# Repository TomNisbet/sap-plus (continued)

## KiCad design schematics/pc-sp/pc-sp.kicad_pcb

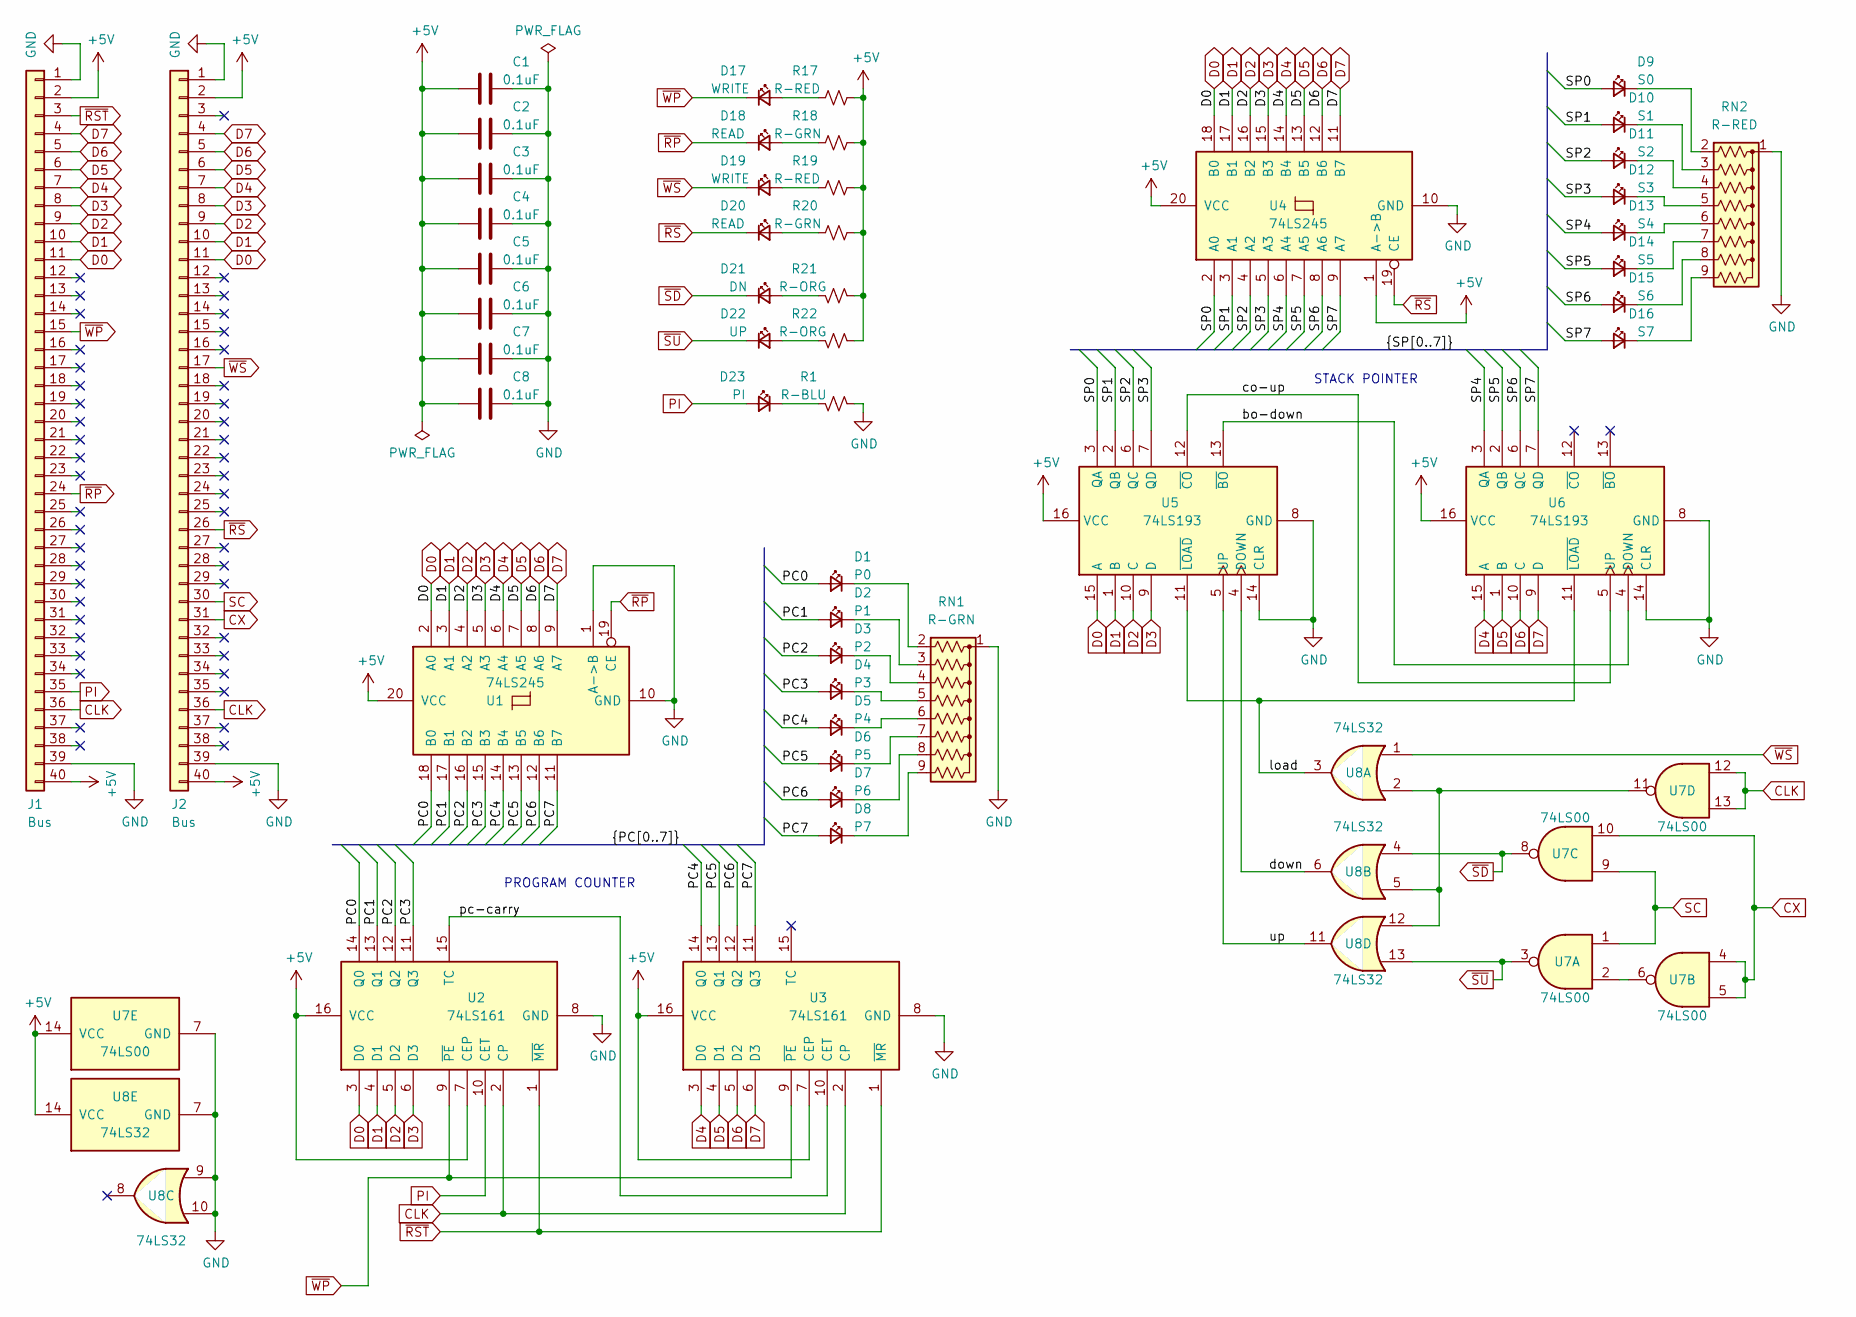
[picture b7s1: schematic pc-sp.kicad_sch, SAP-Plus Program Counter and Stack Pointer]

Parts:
C1, C2, C3, C4, C5, C6, C7, C8: 0.1uF; C_Disc_D3.0mm_W1.6mm_P2.50mm
D1: P0; LED_D3.0mm
D2: P1; LED_D3.0mm
D3: P2; LED_D3.0mm
D4: P3; LED_D3.0mm
D5: P4; LED_D3.0mm
D6: P5; LED_D3.0mm
D7: P6; LED_D3.0mm
D8: P7; LED_D3.0mm
D9: S0; LED_D3.0mm
D10: S1; LED_D3.0mm
D11: S2; LED_D3.0mm
D12: S3; LED_D3.0mm
D13: S4; LED_D3.0mm
D14: S5; LED_D3.0mm
D15: S6; LED_D3.0mm
D16: S7; LED_D3.0mm
D17, D19: WRITE; LED_D3.0mm
D18, D20: READ; LED_D3.0mm
D21: DN; LED_D3.0mm
D22: UP; LED_D3.0mm
D23: PI; LED_D3.0mm
J1, J2: Bus; PinHeader_1x40_P2.54mm_Vertical
R1: R-BLU; R_Axial_DIN0207_L6.3mm_D2.5mm_P10.16mm_Horizontal
R17, R19: R-RED; R_Axial_DIN0207_L6.3mm_D2.5mm_P10.16mm_Horizontal
R18, R20: R-GRN; R_Axial_DIN0207_L6.3mm_D2.5mm_P10.16mm_Horizontal
R21, R22: R-ORG; R_Axial_DIN0207_L6.3mm_D2.5mm_P10.16mm_Horizontal
RN1: R-GRN; R_Array_SIP9
RN2: R-RED; R_Array_SIP9
U1, U4: 74LS245; DIP-20_W7.62mm
U2, U3: 74LS161; DIP-16_W7.62mm
U5, U6: 74LS193; DIP-16_W7.62mm
U7: 74LS00; DIP-14_W7.62mm
U8: 74LS32; DIP-14_W7.62mm

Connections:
+5V: C1.2, C2.2, C3.2, C4.2, C5.2, C6.2, C7.2, C8.2, J1.2, J1.40, J2.2, J2.40, R17.1, R18.1, R19.1, R20.1, R21.2, R22.2, U1.20 (VCC), U2.7 (CEP), U2.16 (VCC), U3.7 (CEP), U3.16 (VCC), U4.1 (A->B), U4.20 (VCC), U5.16 (VCC), U6.16 (VCC), U7.14 (VCC), U8.14 (VCC)
/PC0: D1.2 (A), U1.18 (B0), U2.14 (Q0)
/PC1: D2.2 (A), U1.17 (B1), U2.13 (Q1)
/PC2: D3.2 (A), U1.16 (B2), U2.12 (Q2)
/PC3: D4.2 (A), U1.15 (B3), U2.11 (Q3)
/PC4: D5.2 (A), U1.14 (B4), U3.14 (Q0)
/PC5: D6.2 (A), U1.13 (B5), U3.13 (Q1)
/PC6: D7.2 (A), U1.12 (B6), U3.12 (Q2)
/PC7: D8.2 (A), U1.11 (B7), U3.11 (Q3)
/SP0: D9.2 (A), U4.2 (A0), U5.3 (QA)
/SP1: D10.2 (A), U4.3 (A1), U5.2 (QB)
/SP2: D11.2 (A), U4.4 (A2), U5.6 (QC)
/SP3: D12.2 (A), U4.5 (A3), U5.7 (QD)
/SP4: D13.2 (A), U4.6 (A4), U6.3 (QA)
/SP5: D14.2 (A), U4.7 (A5), U6.2 (QB)
/SP6: D15.2 (A), U4.8 (A6), U6.6 (QC)
/SP7: D16.2 (A), U4.9 (A7), U6.7 (QD)
/bo-down: U5.13 (~BO), U6.4 (DOWN)
/co-up: U5.12 (~CO), U6.5 (UP)
/down: U5.4 (DOWN), U8.6
/load: U5.11 (~LOAD), U6.11 (~LOAD), U8.3
/pc-carry: U2.15 (TC), U3.10 (CET)
/up: U5.5 (UP), U8.11
CLK: J1.36, J2.36, U2.2 (CP), U3.2 (CP), U7.12, U7.13
CX: J2.31, U7.4, U7.5, U7.10
D0: J1.11, J2.11, U1.2 (A0), U2.3 (D0), U4.18 (B0), U5.15 (A)
D1: J1.10, J2.10, U1.3 (A1), U2.4 (D1), U4.17 (B1), U5.1 (B)
D2: J1.9, J2.9, U1.4 (A2), U2.5 (D2), U4.16 (B2), U5.10 (C)
D3: J1.8, J2.8, U1.5 (A3), U2.6 (D3), U4.15 (B3), U5.9 (D)
D4: J1.7, J2.7, U1.6 (A4), U3.3 (D0), U4.14 (B4), U6.15 (A)
D5: J1.6, J2.6, U1.7 (A5), U3.4 (D1), U4.13 (B5), U6.1 (B)
D6: J1.5, J2.5, U1.8 (A6), U3.5 (D2), U4.12 (B6), U6.10 (C)
D7: J1.4, J2.4, U1.9 (A7), U3.6 (D3), U4.11 (B7), U6.9 (D)
GND: C1.1, C2.1, C3.1, C4.1, C5.1, C6.1, C7.1, C8.1, J1.1, J1.39, J2.1, J2.39, R1.2, RN1.1 (common), RN2.1 (common), U1.1 (A->B), U1.10 (GND), U2.8 (GND), U3.8 (GND), U4.10 (GND), U5.8 (GND), U5.14 (CLR), U6.8 (GND), U6.14 (CLR), U7.7 (GND), U8.7 (GND), U8.9, U8.10
unnamed: D1.1 (K), RN1.2 (R1)
unnamed: D2.1 (K), RN1.3 (R2)
unnamed: D3.1 (K), RN1.4 (R3)
unnamed: D4.1 (K), RN1.5 (R4)
unnamed: D5.1 (K), RN1.6 (R5)
unnamed: D6.1 (K), RN1.7 (R6)
unnamed: D7.1 (K), RN1.8 (R7)
unnamed: D8.1 (K), RN1.9 (R8)
unnamed: D9.1 (K), RN2.2 (R1)
unnamed: D10.1 (K), RN2.3 (R2)
unnamed: D11.1 (K), RN2.4 (R3)
unnamed: D12.1 (K), RN2.5 (R4)
unnamed: D13.1 (K), RN2.6 (R5)
unnamed: D14.1 (K), RN2.7 (R6)
unnamed: D15.1 (K), RN2.8 (R7)
unnamed: D16.1 (K), RN2.9 (R8)
unnamed: D17.2 (A), R17.2
unnamed: D18.2 (A), R18.2
unnamed: D19.2 (A), R19.2
unnamed: D20.2 (A), R20.2
unnamed: D21.2 (A), R21.1
unnamed: D22.2 (A), R22.1
unnamed: D23.1 (K), R1.1
unnamed: U7.2, U7.6
unnamed: U7.11, U8.2, U8.5, U8.12
PI: D23.2 (A), J1.35, U2.10 (CET)
SC: J2.30, U7.1, U7.9
~RP: D18.1 (K), J1.24, U1.19 (CE)
~RST: J1.3, U2.1 (~MR), U3.1 (~MR)
~RS: D20.1 (K), J2.26, U4.19 (CE)
~SD: D21.1 (K), U7.8, U8.4
~SU: D22.1 (K), U7.3, U8.13
~WP: D17.1 (K), J1.15, U2.9 (~PE), U3.9 (~PE)
~WS: D19.1 (K), J2.17, U8.1

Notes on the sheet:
PROGRAM COUNTER
STACK POINTER

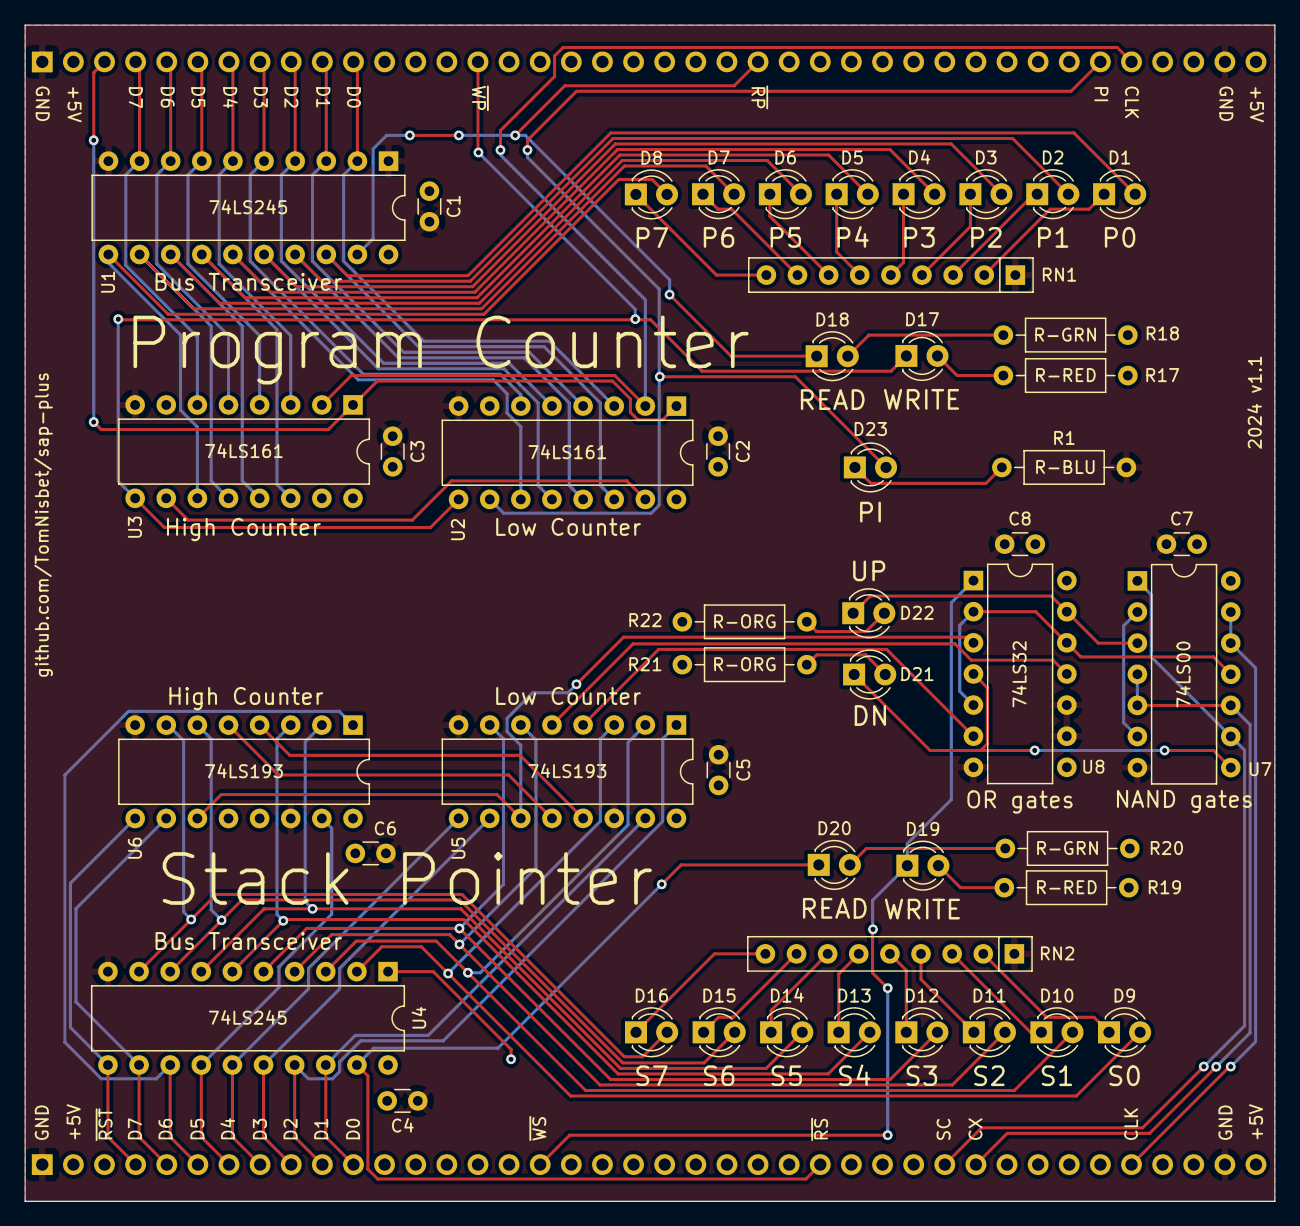
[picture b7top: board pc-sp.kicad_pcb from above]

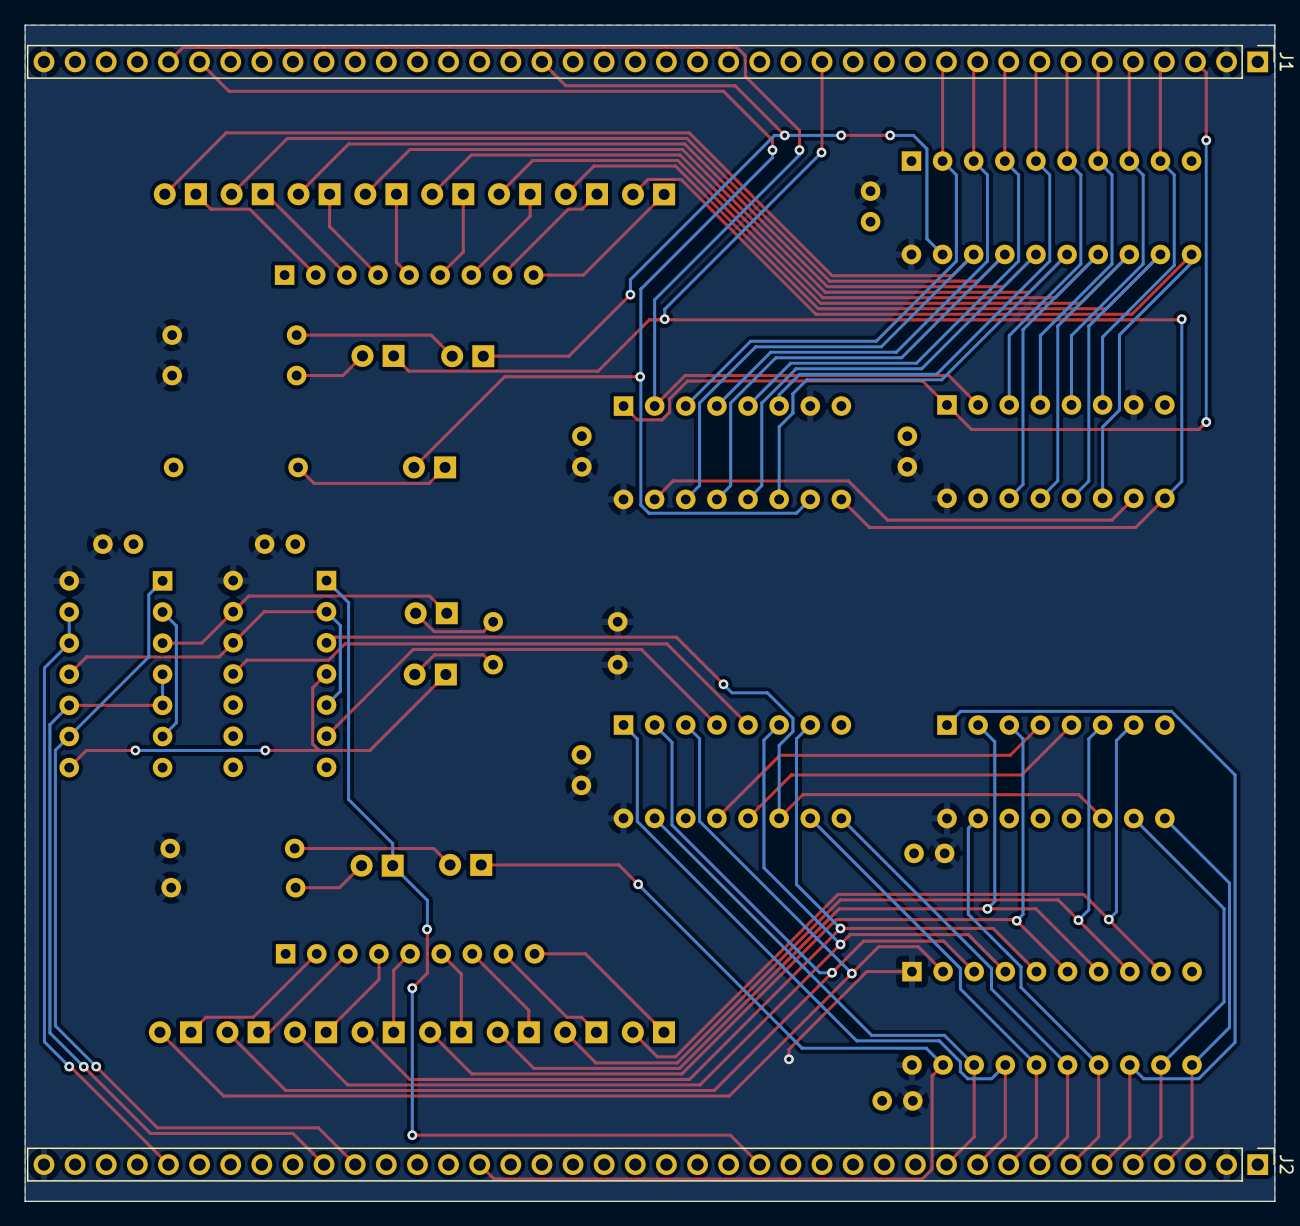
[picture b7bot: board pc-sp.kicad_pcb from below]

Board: 2 copper layers, 102.0 x 96.0 mm, 50 parts (2 on the bottom side), 68 nets.

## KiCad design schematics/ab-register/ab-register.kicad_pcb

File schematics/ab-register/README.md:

# A and B Register Module schematics

created with KiCad 8.0

## Changelog

### 1.1

* Fix polarity of BI LED
* Add module interconnect labels
* Add BI text box

### 1.0

* Initial version

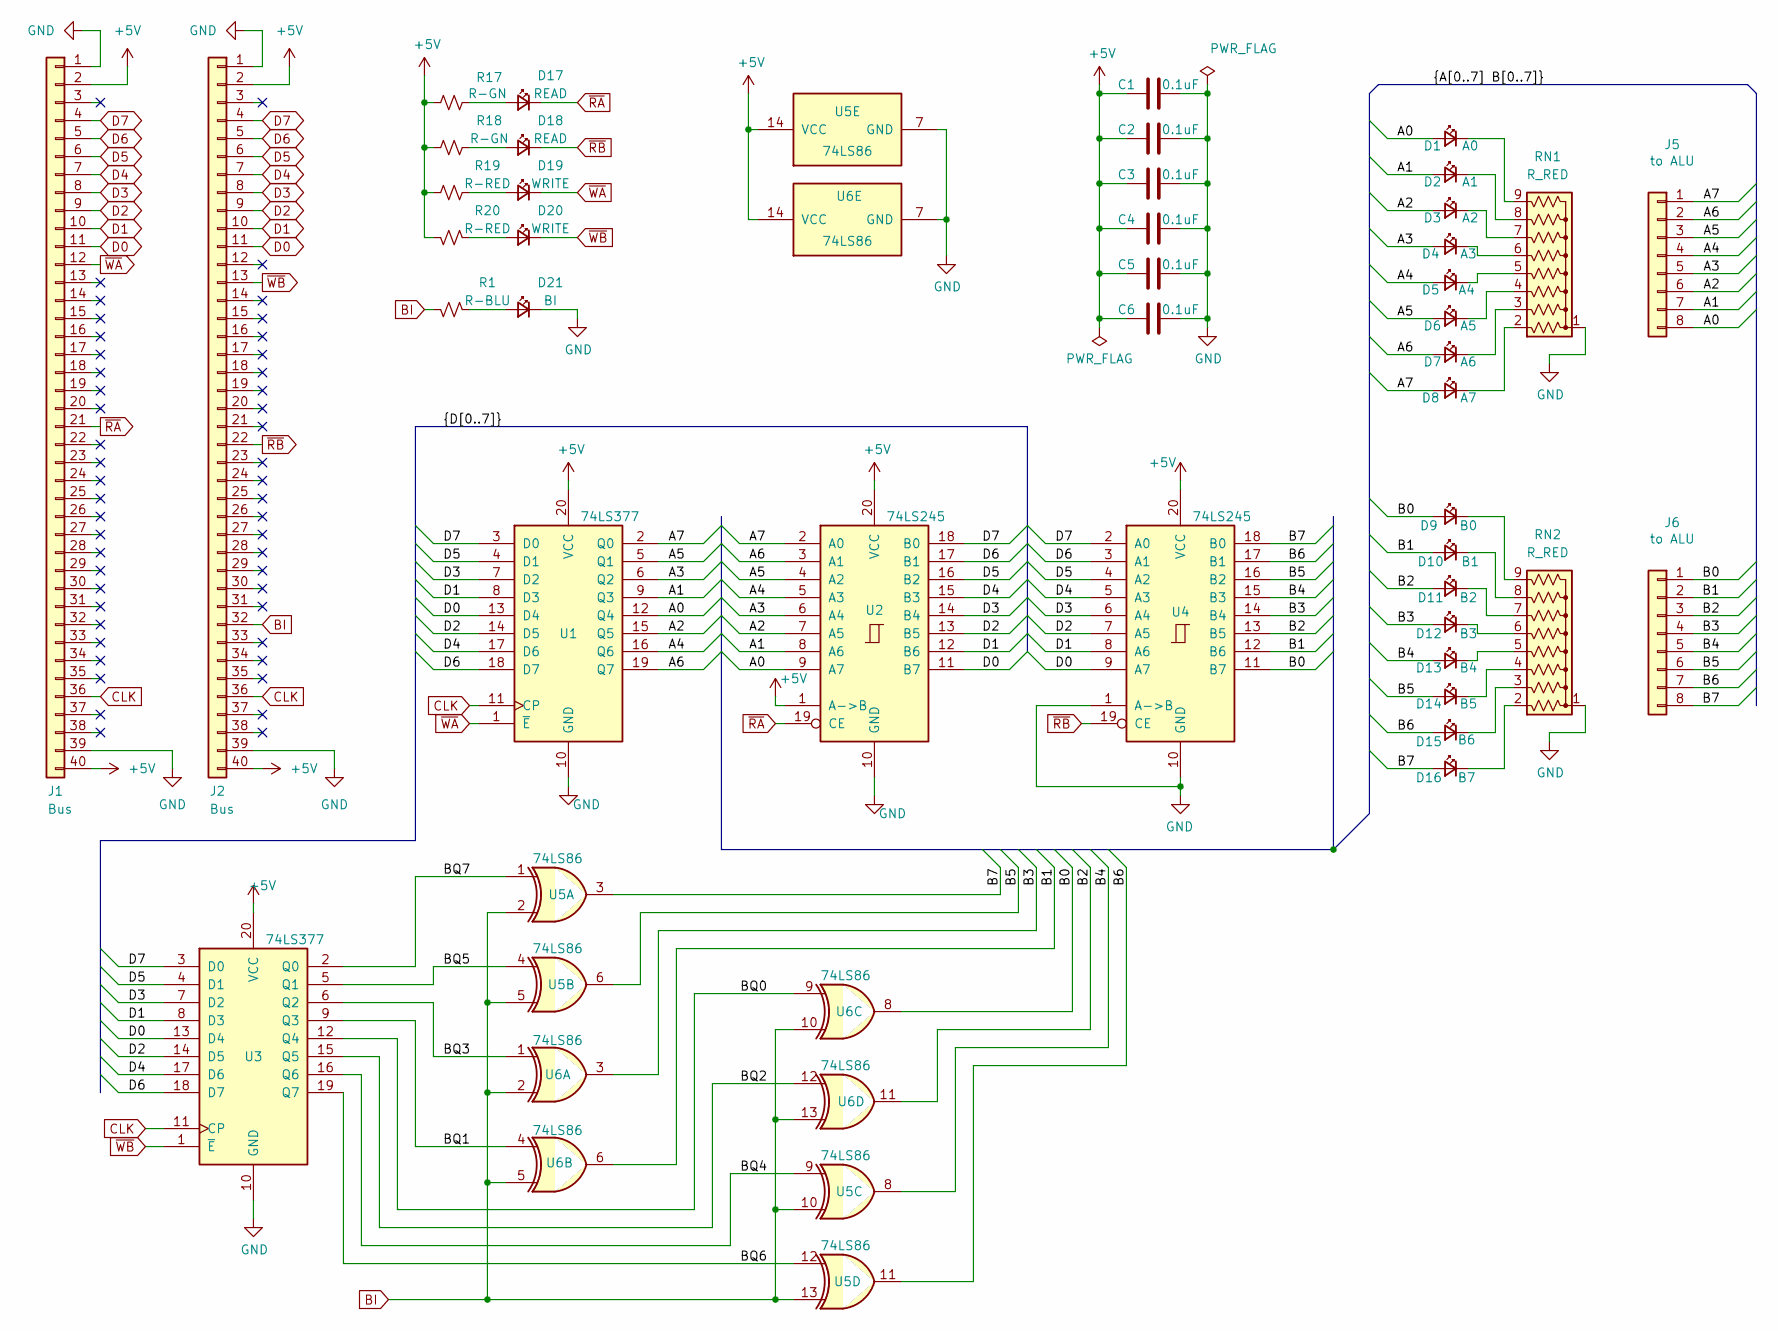
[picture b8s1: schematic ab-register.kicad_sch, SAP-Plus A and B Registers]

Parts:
C1, C2, C3, C4, C5, C6: 0.1uF; C_Disc_D3.0mm_W1.6mm_P2.50mm
D1: A0; LED_D3.0mm
D2: A1; LED_D3.0mm
D3: A2; LED_D3.0mm
D4: A3; LED_D3.0mm
D5: A4; LED_D3.0mm
D6: A5; LED_D3.0mm
D7: A6; LED_D3.0mm
D8: A7; LED_D3.0mm
D9: B0; LED_D3.0mm
D10: B1; LED_D3.0mm
D11: B2; LED_D3.0mm
D12: B3; LED_D3.0mm
D13: B4; LED_D3.0mm
D14: B5; LED_D3.0mm
D15: B6; LED_D3.0mm
D16: B7; LED_D3.0mm
D17, D18: READ; LED_D3.0mm
D19, D20: WRITE; LED_D3.0mm
D21: BI; LED_D3.0mm
J1, J2: Bus; PinHeader_1x40_P2.54mm_Vertical
J5, J6: to ALU; PinHeader_1x08_P2.54mm_Vertical
R1: R-BLU; R_Axial_DIN0207_L6.3mm_D2.5mm_P10.16mm_Horizontal
R17, R18: R-GN; R_Axial_DIN0207_L6.3mm_D2.5mm_P10.16mm_Horizontal
R19, R20: R-RED; R_Axial_DIN0207_L6.3mm_D2.5mm_P10.16mm_Horizontal
RN1, RN2: R_RED; R_Array_SIP9
U1, U3: 74LS377; DIP-20_W7.62mm
U2, U4: 74LS245; DIP-20_W7.62mm
U5, U6: 74LS86; DIP-14_W7.62mm

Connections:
+5V: C1.2, C2.2, C3.2, C4.2, C5.2, C6.2, J1.2, J1.40, J2.2, J2.40, R17.2, R18.2, R19.2, R20.1, U1.20 (VCC), U2.1 (A->B), U2.20 (VCC), U3.20 (VCC), U4.20 (VCC), U5.14 (VCC), U6.14 (VCC)
/A0: D1.2 (A), J5.8, U1.12 (Q4), U2.9 (A7)
/A1: D2.2 (A), J5.7, U1.9 (Q3), U2.8 (A6)
/A2: D3.2 (A), J5.6, U1.15 (Q5), U2.7 (A5)
/A3: D4.2 (A), J5.5, U1.6 (Q2), U2.6 (A4)
/A4: D5.2 (A), J5.4, U1.16 (Q6), U2.5 (A3)
/A5: D6.2 (A), J5.3, U1.5 (Q1), U2.4 (A2)
/A6: D7.2 (A), J5.2, U1.19 (Q7), U2.3 (A1)
/A7: D8.2 (A), J5.1, U1.2 (Q0), U2.2 (A0)
/B0: D9.2 (A), J6.1, U4.11 (B7), U6.8
/B1: D10.2 (A), J6.2, U4.12 (B6), U6.6
/B2: D11.2 (A), J6.3, U4.13 (B5), U6.11
/B3: D12.2 (A), J6.4, U4.14 (B4), U6.3
/B4: D13.2 (A), J6.5, U4.15 (B3), U5.8
/B5: D14.2 (A), J6.6, U4.16 (B2), U5.6
/B6: D15.2 (A), J6.7, U4.17 (B1), U5.11
/B7: D16.2 (A), J6.8, U4.18 (B0), U5.3
/BQ0: U3.12 (Q4), U6.9
/BQ1: U3.9 (Q3), U6.4
/BQ2: U3.15 (Q5), U6.12
/BQ3: U3.6 (Q2), U6.1
/BQ4: U3.16 (Q6), U5.9
/BQ5: U3.5 (Q1), U5.4
/BQ6: U3.19 (Q7), U5.12
/BQ7: U3.2 (Q0), U5.1
BI: J2.32, R1.1, U5.2, U5.5, U5.10, U5.13, U6.2, U6.5, U6.10, U6.13
CLK: J1.36, J2.36, U1.11 (CP), U3.11 (CP)
D0: J1.11, J2.11, U1.13 (D4), U2.11 (B7), U3.13 (D4), U4.9 (A7)
D1: J1.10, J2.10, U1.8 (D3), U2.12 (B6), U3.8 (D3), U4.8 (A6)
D2: J1.9, J2.9, U1.14 (D5), U2.13 (B5), U3.14 (D5), U4.7 (A5)
D3: J1.8, J2.8, U1.7 (D2), U2.14 (B4), U3.7 (D2), U4.6 (A4)
D4: J1.7, J2.7, U1.17 (D6), U2.15 (B3), U3.17 (D6), U4.5 (A3)
D5: J1.6, J2.6, U1.4 (D1), U2.16 (B2), U3.4 (D1), U4.4 (A2)
D6: J1.5, J2.5, U1.18 (D7), U2.17 (B1), U3.18 (D7), U4.3 (A1)
D7: J1.4, J2.4, U1.3 (D0), U2.18 (B0), U3.3 (D0), U4.2 (A0)
GND: C1.1, C2.1, C3.1, C4.1, C5.1, C6.1, D21.1 (K), J1.1, J1.39, J2.1, J2.39, RN1.1 (common), RN2.1 (common), U1.10 (GND), U2.10 (GND), U3.10 (GND), U4.1 (A->B), U4.10 (GND), U5.7 (GND), U6.7 (GND)
unnamed: D1.1 (K), RN1.9 (R8)
unnamed: D2.1 (K), RN1.8 (R7)
unnamed: D3.1 (K), RN1.7 (R6)
unnamed: D4.1 (K), RN1.6 (R5)
unnamed: D5.1 (K), RN1.5 (R4)
unnamed: D6.1 (K), RN1.4 (R3)
unnamed: D7.1 (K), RN1.3 (R2)
unnamed: D8.1 (K), RN1.2 (R1)
unnamed: D9.1 (K), RN2.9 (R8)
unnamed: D10.1 (K), RN2.8 (R7)
unnamed: D11.1 (K), RN2.7 (R6)
unnamed: D12.1 (K), RN2.6 (R5)
unnamed: D13.1 (K), RN2.5 (R4)
unnamed: D14.1 (K), RN2.4 (R3)
unnamed: D15.1 (K), RN2.3 (R2)
unnamed: D16.1 (K), RN2.2 (R1)
unnamed: D17.2 (A), R17.1
unnamed: D18.2 (A), R18.1
unnamed: D19.2 (A), R19.1
unnamed: D20.2 (A), R20.2
unnamed: D21.2 (A), R1.2
~RA: D17.1 (K), J1.21, U2.19 (CE)
~RB: D18.1 (K), J2.22, U4.19 (CE)
~WA: D19.1 (K), J1.12, U1.1 (~E)
~WB: D20.1 (K), J2.13, U3.1 (~E)

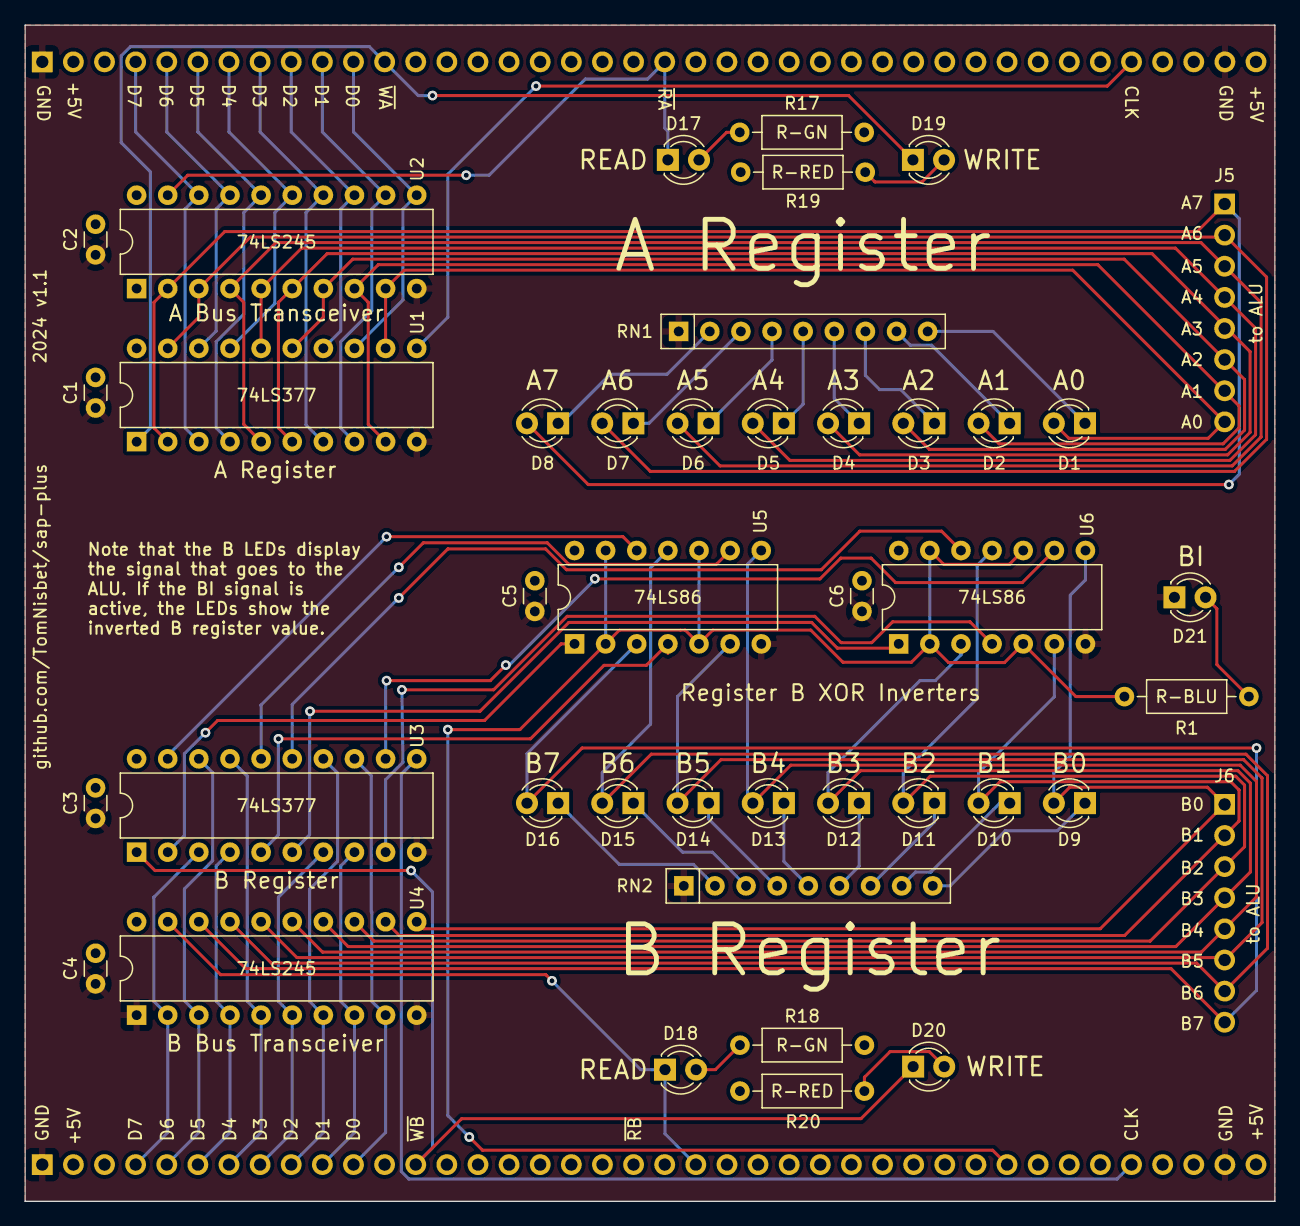
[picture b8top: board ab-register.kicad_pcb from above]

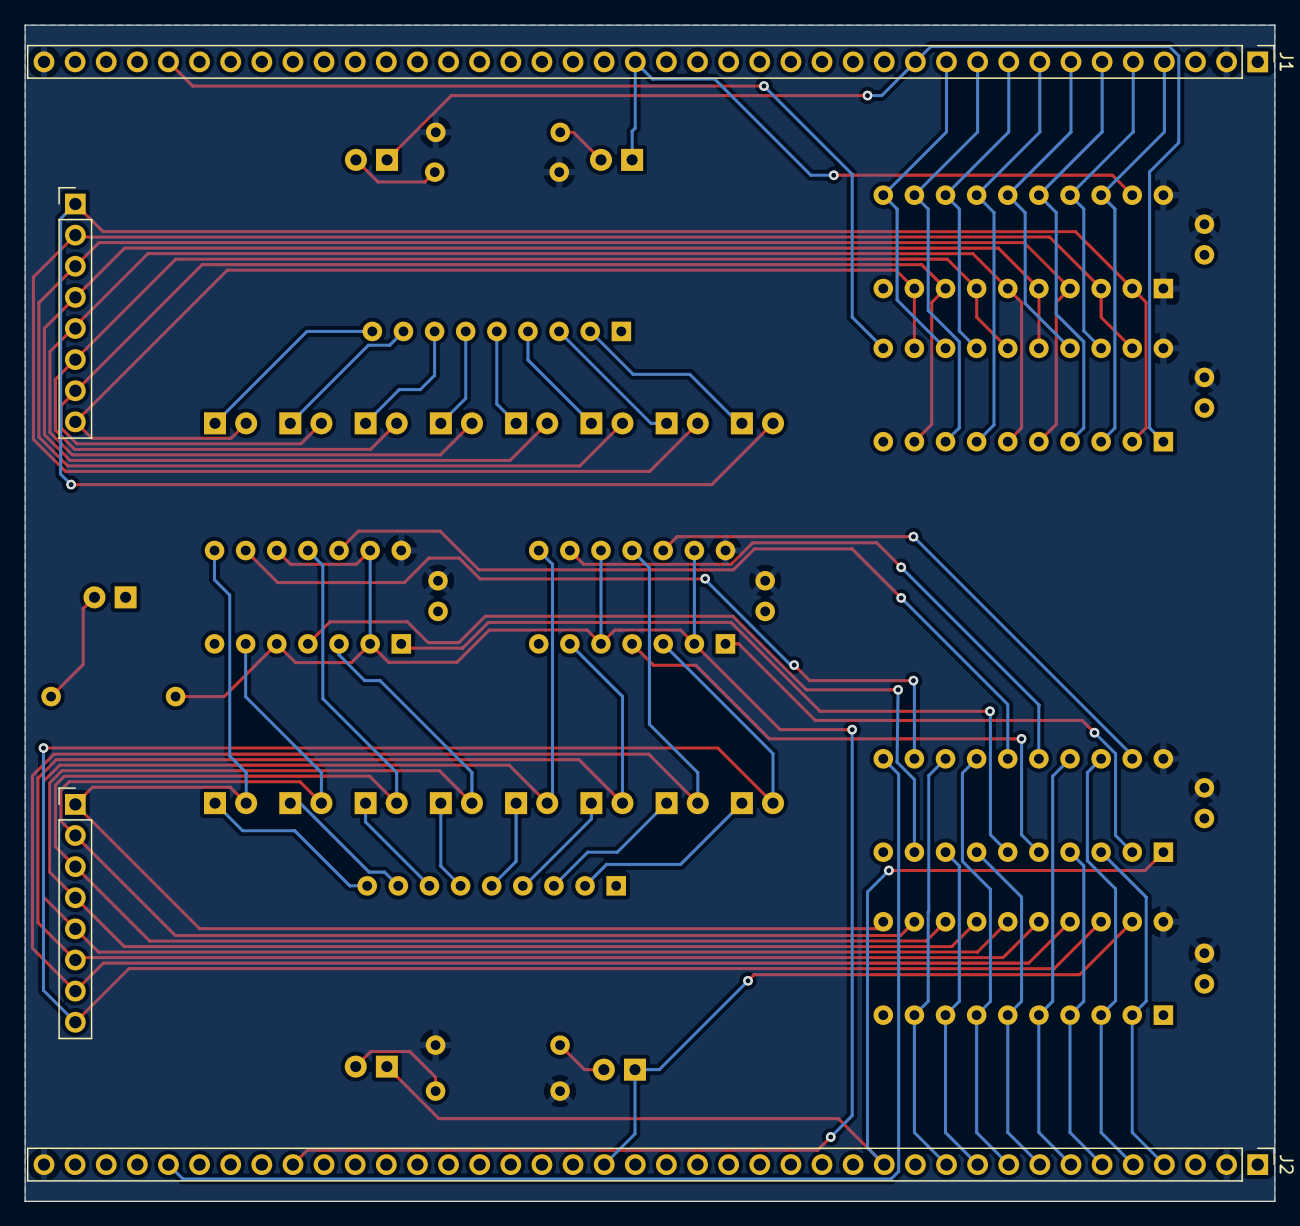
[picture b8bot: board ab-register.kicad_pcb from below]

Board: 2 copper layers, 102.0 x 96.0 mm, 44 parts (4 on the bottom side), 61 nets.

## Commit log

2024-10-04 initial checkin
2024-10-04 missing config files for docs
2024-10-16 add instruction list and tools to docs
2024-10-30 add arduino-loader and docs for laoder and backplane
2024-11-17 docs add bus signals list
2024-11-28 add microcode, update loader OLED
2024-11-30 Add schematics for bus-connect and module template
2024-11-30 add backplane schematic
2024-11-30 remove temp files
2024-11-30 add clock and output register schematics
2024-12-01 add microcode module schematic
2024-12-01 add RAM and MAR module schematic
2024-12-01 add AB register module schematics
2024-12-01 add PC and SP module schematics
2024-12-01 Add Instruction Resister and Step Counter schematics
2024-12-01 Add Loader Module scematics
2024-12-01 Add ALU Module schematics
2024-12-01 swap labels on Clock Module RUN/SSTOP switch
2024-12-05 wrong project name in docs config file
2024-12-06 Change Loader reset button
2024-12-13 add schematic images to docs
2024-12-27 add module template docs
2024-12-27 change to mmistakes repo
2024-12-27 update template schematic and docs with interconnect notes
2024-12-28 clock module docs
2024-12-28 add IR-SC docs
2024-12-29 add RAM-MAR module docs
2024-12-30 Add Program Counter and Stack Pointer docs
2024-12-30 add AB Register docs
2024-12-31 Add ALU Molude docs
2025-01-10 fix microcode bugs
2025-01-21 fix subtraction and compare instruction descriptions
2025-01-22 create worlds worst assembler
2025-01-23 assembler and test program updates
2025-01-24 swap SP count direction; add CYN instruction
2025-01-25 update output formats of wwasm; add program names to Loader
2025-01-27 move loader asm examples to separate files; add instruction aliases and new LAX,SAX,DCS,INS instructions
2025-01-27 fix broken conditional branch instructions
2025-01-27 include updated fibonacci.asm code in Loader
2025-01-31 add Output Register documentation
2025-02-01 add support for negative constants to wwasm; add squares.asm
2025-02-01 add squares.asm to Loader
2025-02-01 typo in ADI description
2025-02-01 add Demo Mode to the Arduino Loader
2025-02-03 move the utilities to the top-level directory and add docs for it
2025-02-18 add UI changes to demo mode
2025-03-09 instruction cycle docs
2025-03-09 docs for instruction cycle and EEPROM glitch
2025-03-26 add demo gif
2025-05-16 add IR2 description to timing docs
2025-05-24 clock module 2.0 - adds clock divider
2025-05-26 add PC contents to instruction cycle timing diagram
2025-05-26 update instruction timing docs
2025-05-27 document the clock-reset problem
2025-05-28 document the version 2.0 clock module
2025-06-12 document loader demo mode
2025-07-01 draft memory loader docs
2025-07-04 update draft memory loader docs
2025-07-17 Memory Loader version 3.0
2025-07-19 cleanup utilities diretory
2025-07-20 typo in DCS and INS instruction descriptions
2025-07-20 Arduino Loader Module v1.2 schematics and code
2025-07-22 clean up docs
2025-07-27 fix SAP-1 error in clock-reset doc
